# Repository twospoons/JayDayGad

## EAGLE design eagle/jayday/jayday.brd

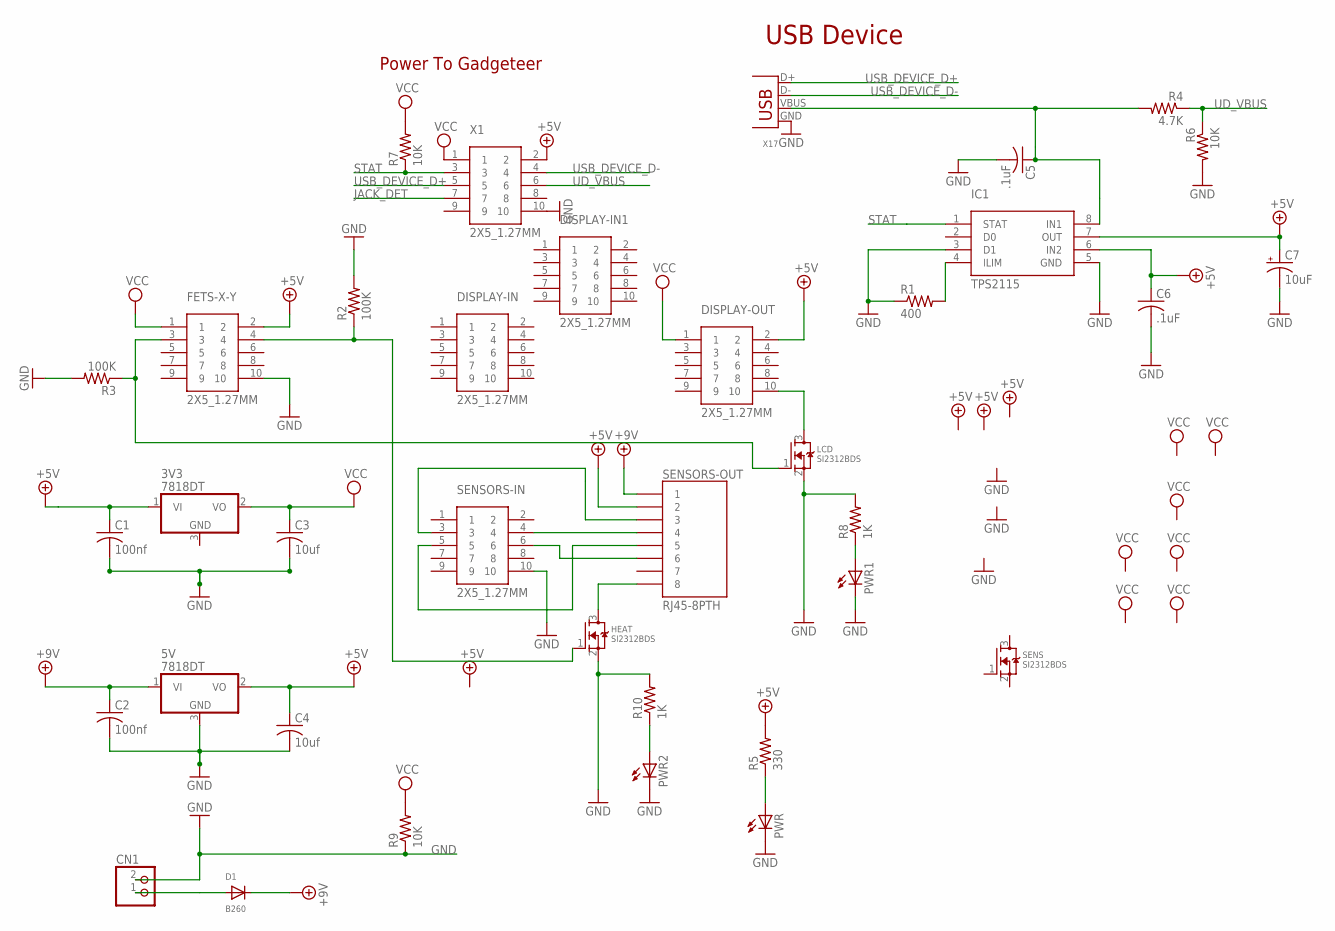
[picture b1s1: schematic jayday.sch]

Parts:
3V3, 5V: 7818DT; TO252
C1, C2: 100nf; C0805
C3, C4: 10uf; C0805
C5, C6: .1uF; C0603K
C7: 10uF; CT3528
CN1: JST_2PIN-THM-RA; JST-PH-2-THM-RA
D1: B260; SMADIODE
DISPLAY-IN, DISPLAY-IN1: 2X5_1.27MM
DISPLAY-OUT: 2X5_1.27MM
FETS-X-Y: 2X5_1.27MM
HEAT: SI2312BDS; TO-236
IC1: TPS2115; TSSOP8
LCD: SI2312BDS; TO-236
PWR, PWR1, PWR2: LEDCHIPLED_0805; CHIPLED_0805
R1: 400; R0603
R2, R3: 100K; R0603
R4: 4.7K; R0603
R5: 330; R0603
R6, R7, R9: 10K; R0603
R8, R10: 1K; R0603
SENS: SI2312BDS; TO-236
SENSORS-IN: 2X5_1.27MM
SENSORS-OUT: RJ45-8PTH; RJ45-8
X1: 2X5_1.27MM
X17: DX2R005HN2E700; USB-MB-S

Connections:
+5V: 3V3.1 (VI), 5V.2 (VO), C1.1, C4.1, C6.1, C7.+, DISPLAY-OUT.2, FETS-X-Y.2, IC1.6 (IN2), IC1.7 (OUT), R5.2, SENSORS-OUT.2, X1.2
+9V: 5V.1 (VI), C2.1, D1.C, SENSORS-OUT.1
GND: 5V.3 (GND), C1.2, C2.2, C3.2, C4.2, C5.2, C6.2, C7.-, CN1.2 (1), FETS-X-Y.10, HEAT.2 (S), IC1.3 (D1), IC1.5 (GND), LCD.2 (S), PWR.C, PWR1.C, PWR2.C, R1.1, R2.2, R3.2, R6.2, R8.2, R9.1, R10.2, SENSORS-IN.10, X1.10, X17.GND
JACK_DET: X1.7
unnamed: CN1.1 (2), D1.A
unnamed: PWR.A, R5.1
unnamed: DISPLAY-OUT.10, LCD.3 (D)
unnamed: HEAT.3 (D), SENSORS-OUT.8
unnamed: SENSORS-IN.3, SENSORS-OUT.3
unnamed: SENSORS-IN.4, SENSORS-OUT.4
unnamed: C5.1, IC1.8 (IN1), R4.2, X17.VBUS
unnamed: IC1.4 (ILIM), R1.2
unnamed: SENSORS-IN.5, SENSORS-OUT.5
unnamed: SENSORS-IN.6, SENSORS-OUT.6
unnamed: FETS-X-Y.3, LCD.1 (G), R3.1
unnamed: FETS-X-Y.4, HEAT.1 (G), R2.1
unnamed: PWR1.A, R8.1
unnamed: PWR2.A, R10.1
STAT: IC1.1 (STAT), R7.1, X1.3
UD_VBUS: R4.1, R6.1, X1.6
USB_DEVICE_D+: X1.5, X17.D+
USB_DEVICE_D-: X1.4, X17.D-
VCC: 3V3.2 (VO), C3.1, DISPLAY-OUT.1, FETS-X-Y.1, R7.2, R9.2, X1.1

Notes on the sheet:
USB Device
Power To Gadgeteer

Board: 2 copper layers, 36 parts (0 on the bottom side), 22 nets, no tracks yet.

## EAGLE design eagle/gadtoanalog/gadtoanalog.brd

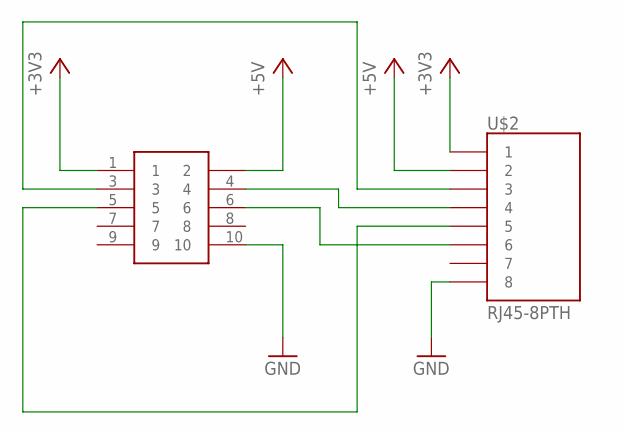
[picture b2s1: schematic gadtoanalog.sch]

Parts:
U$1: SHF105SM; SHF105DSM
U$2: RJ45-8PTH; RJ45-8

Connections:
+3V3: U$1.1, U$2.1
+5V: U$1.2, U$2.2
GND: U$1.10, U$2.8
unnamed: U$1.3, U$2.3
unnamed: U$1.4, U$2.4
unnamed: U$1.5, U$2.5
unnamed: U$1.6, U$2.6

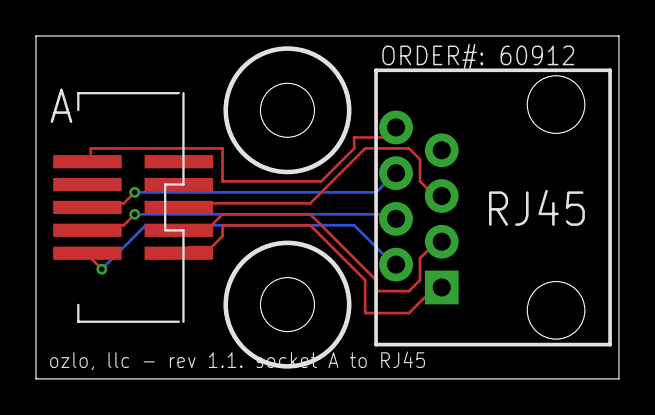
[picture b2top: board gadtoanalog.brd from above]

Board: 2 copper layers, 32.4 x 19.1 mm, 4 parts (0 on the bottom side), 7 nets.

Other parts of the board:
U$3, U$4: DRIL-3

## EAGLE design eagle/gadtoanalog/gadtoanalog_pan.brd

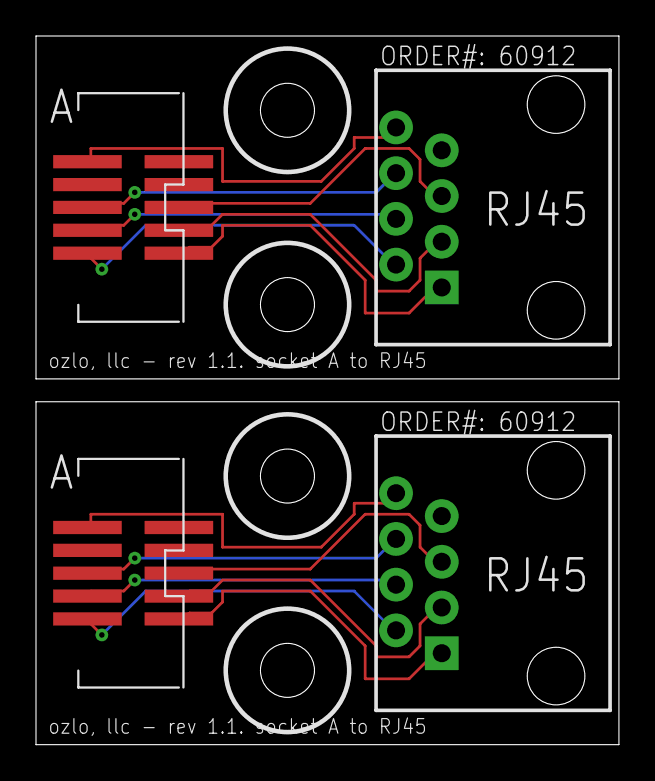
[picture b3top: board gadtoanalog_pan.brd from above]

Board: 2 copper layers, 32.4 x 39.4 mm, 8 parts (0 on the bottom side), 14 nets.

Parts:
U$1, U$8: SHF105SM; SHF105DSM
U$2, U$5: RJ45-8PTH; RJ45-8
U$3, U$4, U$6, U$7: DRIL-3

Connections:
+3V1: U$5.1, U$8.1
+3V3: U$1.1, U$2.1
+5V: U$1.2, U$2.2
+5V1: U$5.2, U$8.2
GND: U$1.10, U$2.8
GND1: U$5.8, U$8.10
unnamed: U$1.3, U$2.3
unnamed: U$1.4, U$2.4
unnamed: U$1.5, U$2.5
unnamed: U$1.6, U$2.6
unnamed: U$5.3, U$8.3
unnamed: U$5.4, U$8.4
unnamed: U$5.5, U$8.5
unnamed: U$5.6, U$8.6

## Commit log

2012-08-26 updated sdk
2012-08-26 added oled display
2012-09-02 removed old project
2012-09-02 added new rev
2012-09-02 testing drawing
2012-09-03 testing oled
2012-09-03 added eagle files for analog rj 45 connector
2012-09-03 added eagle design for rj45 to analog gadgeteer (SM) with pdf for etching
2012-10-07 modified design
2012-10-07 removed oled for LCD display
2012-10-07 added readings for 3 analog sensors
2012-10-07 added design for sim900 to gadgeteer (minimal)
2012-10-07 new designs for rj45 / sim900 for pro pcb service
2012-10-08 redesigned sim900min for pcb production
2012-10-09 added dynamic loading of service assembly for in field update
2012-10-13 added sim900 serial module
2012-10-14 made modem more stable
2012-10-14 fixed pcd design for sim900, made panelized design for production
2012-10-17 added complete board design
2012-10-19 added board with sim900

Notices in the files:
parts and their libraries:
SparkFun-Connectors: Licensing: CC v3.0 Share-Alike You are welcome to use this library for commercial purposes.
